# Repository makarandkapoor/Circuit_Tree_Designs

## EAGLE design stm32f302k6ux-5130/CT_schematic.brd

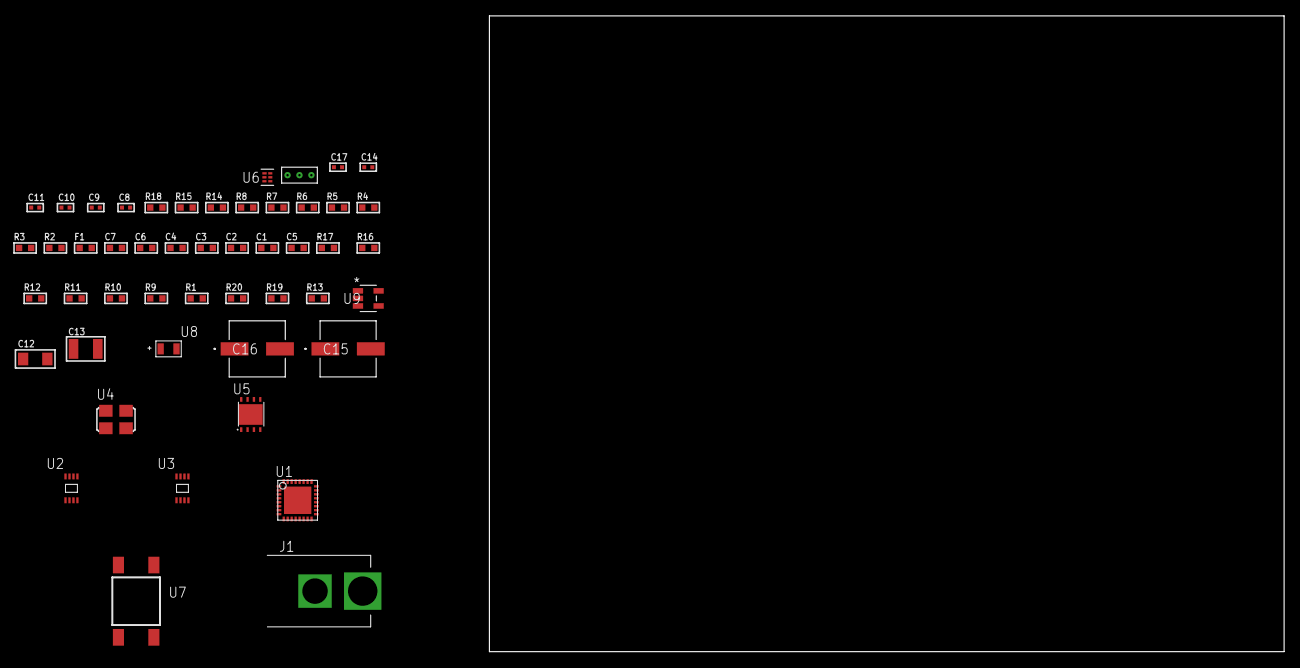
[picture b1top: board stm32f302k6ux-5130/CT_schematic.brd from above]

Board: 2 copper layers, 100.0 x 80.0 mm, 49 parts (0 on the bottom side), 25 nets, no tracks yet.

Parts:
C1, C2, C3, C4: 1e-07; C0603
C5: 4.7e-06; C0603
C6: 1e-08; C0603
C7: 1e-06; C0603
C8, C9, C10, C11, C17: 1e-08; C0402
C12: 1e-05; C1206
C13: 1e-05; C1210
C14: 1e-07; C0402
C15, C16: 0.0001; EXV-9H
F1: 240.0; L0603
J1: PJ-037B; PJ-037B_PACKAGE
R1, R9, R10, R11, R12, R16, R17: 10000.0; R0603
R2, R15: 1000.0; R0603
R3: 1600.5; R0603
R4: 4700.0; R0603
R5, R6, R7, R8: 2200.0; R0603
R13: 100000.0; R0603
R14: 2231.0; R0603
R18: 9100.0; R0603
R19: 680000.0; R0603
R20: 120000.0; R0603
U1: STM32F302K6U6; UFQFPN32
U2: 24AA00T-I/MNY; TDFN-8/6MM
U3: 24AA128T-I/MNY; TDFN-8/6MM
U4: ASFL1-25MHZ-NCS; ASFL1
U5: LP3878SDX-ADJ/NOPB; WSON-8
U6: TPS3895ADRYR; SON-6
U7: 4-1437565-2; SW_4-1437565-2
U8: Q65110A2395; LGM67K-G1J2-24-Z
U9: nc7sz125m5x; NC7SZ125M5X
U10: Dummy; DUMMY_PACKAGE_103

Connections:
CLK_U1_2: U1.2, U4.3
GND: C1.2, C2.2, C3.2, C4.2, C5.2, C6.2, C7.2, C8.2, C9.2, C10.2, C11.2, C12.2, C13.2, C14.2, C15.2, C16.2, C17.2, J1.2, R2.2, R9.2, R12.2, R15.2, R18.2, R20.2, U1.6, U1.16, U1.32, U1.EPAD, U2.4, U3.4, U4.2, U5.3, U5.PAD, U6.2, U8.C, U9.1, U9.3, U10.1
NET_U1_3: R7.1, U1.3, U2.6
NET_U1_4: R4.1, U1.4, U9.4
NET_U1_5: C6.1, C7.1, F1.1, U1.5
NET_U1_20: R8.1, U1.20, U2.5
NET_U1_24: R6.1, U1.24, U3.5
NET_U1_25: R5.1, U1.25, U3.6
NET_U1_29: R3.1, U1.29, U8.A
NET_U1_30: R1.1, U1.30, U7.3, U7.4
NET_U1_31: R9.1, U1.31
NET_U3_1: R10.1, U3.1
NET_U3_2: R11.1, U3.2
NET_U3_3: R12.1, U3.3
NET_U5_1: C11.1, U5.1
NET_U5_6: R14.2, R15.1, U5.6
NET_U5_8: R13.1, U5.8
NET_U6_1: R17.1, R18.1, U6.1
NET_U6_3: R19.2, R20.1, U6.3
NET_U6_4: R16.1, U6.4, U9.2
NET_U7_1: R2.1, U7.1, U7.2
PROC_PA0: U1.7, U10.2
PROC_PA1: U1.8, U10.3
VCC_S1_7V8: C12.1, C15.1, C16.1, J1.1, R13.2, U5.4
VCC_TIER1_3V3: C1.1, C2.1, C3.1, C4.1, C5.1, C8.1, C9.1, C10.1, C13.1, C14.1, C17.1, F1.2, R1.2, R3.2, R4.2, R5.2, R6.2, R7.2, R8.2, R10.2, R11.2, R14.1, R16.2, R17.2, R19.1, U1.1, U1.17, U2.8, U3.7, U3.8, U4.4, U5.5, U6.6, U9.5

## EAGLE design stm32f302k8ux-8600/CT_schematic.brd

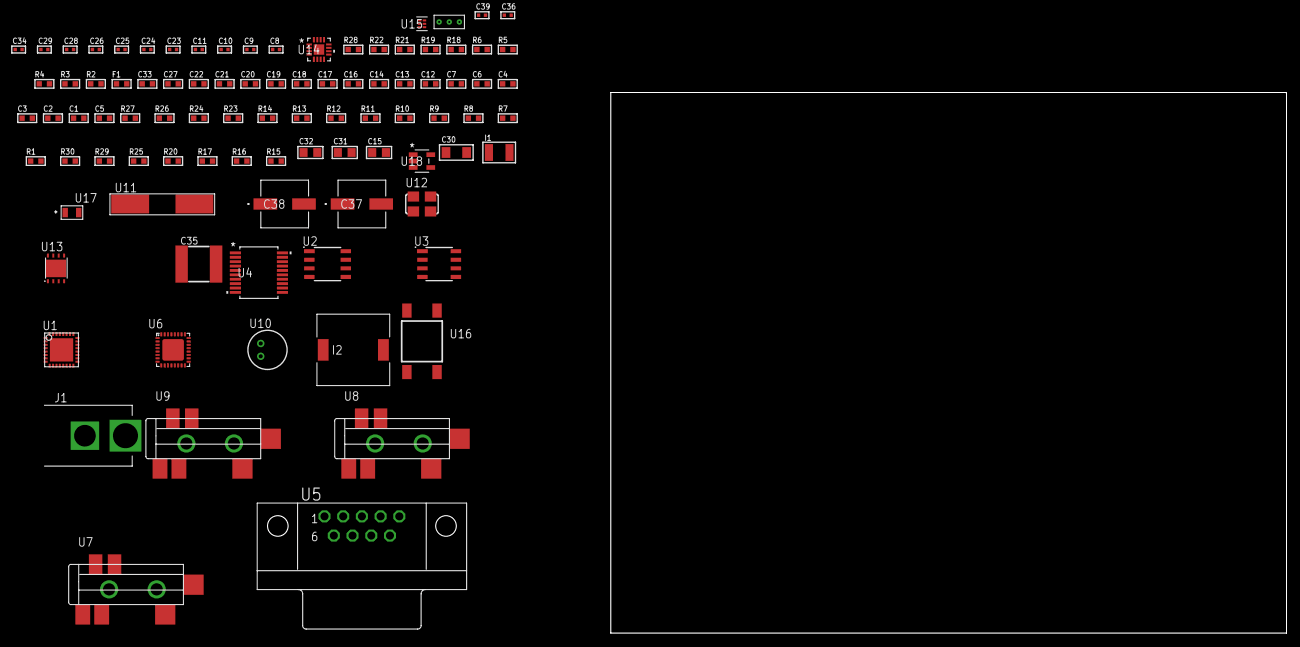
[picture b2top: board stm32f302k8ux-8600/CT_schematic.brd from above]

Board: 2 copper layers, 100.0 x 80.0 mm, 92 parts (0 on the bottom side), 71 nets, no tracks yet.

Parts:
C1, C2, C3, C4: 1e-07; C0603
C5: 4.7e-06; C0603
C6: 1e-08; C0603
C7, C12, C13, C14, C16, C17, C18, C19, C20, C21, C22, C27, C33: 1e-06; C0603
C8, C9: 1e-11; C0402
C10, C11, C28, C29, C39: 1e-08; C0402
C15: 4.7e-06; C0805
C23, C24, C25, C26, C34, C36: 1e-07; C0402
C30: 1e-05; C1206
C31, C32: 1e-05; C0805
C35: 6.8e-05; 2220
C37, C38: 0.0001; EXV-9H
F1: 240.0; L0603
I1: 1.5e-05; L1210
I2: 2.5e-06; DR1040
J1: PJ-037B; PJ-037B_PACKAGE
R1, R7, R8, R9, R10, R11, R12, R13, R14, R26, R27: 10000.0; R0603
R2, R22: 1000.0; R0603
R3: 1600.5; R0603
R4: 4700.0; R0603
R5, R6: 2200.0; R0603
R15, R16, R17, R20: 100000.0; R0603
R18, R19: 1270.0; R0603
R21: 200.0; R0603
R23: 20000.0; R0603
R24: 91000.0; R0603
R25: 300000.0; R0603
R28: 9100.0; R0603
R29: 680000.0; R0603
R30: 120000.0; R0603
U1: STM32F302K8U7; UFQFPN32
U2: AT25160B-SSHL-T; SOIC-8
U3: AT24C02D-SSHM-T; AT24C02D
U4: MAX3218EAP+T; SSOP-20
U5: 182-009-113R531; 182-009-MALE
U6: SGTL5000XNAA3; QFN-32
U7, U8, U9: SJ-43515TS-SMT-TR
U10: WM-64PCT; WM-64PC
U11: ABLS-25.000MHZ-B2F-T
U12: ASFL-24.57MHZ-NCS; ASFL1
U13: LP3878SDX-ADJ/NOPB; WSON-8
U14: LTC3601EUD#PBF; QFN-16_EP
U15: TPS3895ADRYR; SON-6
U16: 4-1437565-2; SW_4-1437565-2
U17: Q65110A2395; LGM67K-G1J2-24-Z
U18: nc7sz125m5x; NC7SZ125M5X
U19: Dummy; DUMMY_PACKAGE_184

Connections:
CLK_CRYSTAL_U1_2: C8.1, U1.2, U11.1
CLK_CRYSTAL_U1_3: C9.1, U1.3, U11.2
CLK_U6_21: U6.21, U12.3
GND: C1.2, C2.2, C3.2, C4.2, C5.2, C6.2, C7.2, C8.2, C9.2, C10.2, C11.2, C12.2, C13.2, C14.2, C23.2, C24.2, C25.2, C26.2, C27.2, C28.2, C29.2, C30.2, C31.2, C32.2, C33.2, C35.1, C35.2, C36.2, C37.2, C38.2, C39.2, J1.2, R2.2, R7.2, R11.2, R13.2, R14.2, R19.2, R22.2, R23.2, R25.2, R28.2, R30.2, U1.6, U1.16, U1.32, U1.EPAD, U2.4, U3.4, U4.5, U4.17, U4.20, U5.5, U6.1, U6.3, U6.7, U6.EXP, U8.1, U9.1, U10.2, U12.2, U13.3, U13.PAD, U14.1, U14.9, U14.17, U15.2, U17.C, U18.1, U18.3, U19.1
NET_U1_4: R4.1, U1.4, U18.4
NET_U1_5: C6.1, C7.1, F1.1, U1.5
NET_U1_24: R6.1, U1.24, U3.5
NET_U1_25: R5.1, U1.25, U3.6
NET_U1_29: R3.1, U1.29, U17.A
NET_U1_30: R1.1, U1.30, U16.3, U16.4
NET_U1_31: R7.1, U1.31
NET_U2_1: R9.1, U2.1
NET_U2_3: R8.1, U2.3
NET_U2_7: R10.1, U2.7
NET_U3_1: R12.1, U3.1
NET_U3_2: R13.1, U3.2
NET_U3_3: R14.1, U3.3
NET_U3_7: R11.1, U3.7
NET_U4_1: I1.1, U4.1
NET_U4_2: R15.1, U4.2
NET_U4_3: R16.1, U4.3
NET_U4_4: R17.1, U4.4
NET_U4_15: C14.1, U4.15
NET_U4_16: C15.2, U4.16
NET_U4_18: C15.1, U4.18
NET_U4_19: C13.1, U4.19
NET_U5_2: U4.12, U5.2
NET_U5_3: U4.14, U5.3
NET_U5_7: U4.11, U5.7
NET_U5_8: U4.13, U5.8
NET_U6_10: C26.1, U6.10
NET_U6_29: R18.1, U6.29
NET_U6_31: R19.1, U6.31
NET_U7_1: U6.4, U7.1
NET_U7_2: U6.2, U7.2
NET_U7_5: U6.6, U7.5
NET_U8_2: C17.1, U8.2
NET_U8_5: C16.1, U8.5
NET_U9_2: C19.1, C20.1, U9.2
NET_U9_5: C18.1, U9.5
NET_U9_13: C19.2, C20.2
NET_U10_1: C21.1, C22.1, C27.1, U6.16, U10.1
NET_U10_15: C21.2, C22.2
NET_U13_1: C29.1, U13.1
NET_U13_6: R21.2, R22.1, U13.6
NET_U13_8: R20.1, U13.8
NET_U14_3: C34.2, I2.1, U14.3, U14.4
NET_U14_6: C34.1, U14.6
NET_U14_7: C33.1, U14.7, U14.12
NET_U14_10: R25.1, U14.10
NET_U14_11: R23.1, R24.1, U14.11
NET_U14_ATNET_3: I2.2, R24.2
NET_U15_1: R27.1, R28.1, U15.1
NET_U15_3: R29.2, R30.1, U15.3
NET_U15_4: R26.1, U15.4, U18.2
NET_U16_1: R2.1, U16.1, U16.2
PROC_I2S3_CK: U1.26, U6.24
PROC_I2S3_EXT_SD: U1.27, U6.25
PROC_I2S3_SD: U1.28, U6.26
PROC_I2S3_WS: U1.11, U6.23
PROC_PA5: U1.12, U19.2
PROC_PA6: U1.13, U19.3
PROC_SPI2_MISO: U1.20, U2.2
PROC_SPI2_MOSI: U1.21, U2.5
PROC_USART2_CTS: U1.7, U4.8
PROC_USART2_RTS: U1.8, U4.10
PROC_USART2_RX: U1.10, U4.9
PROC_USART2_TX: U1.9, U4.7
VCC_S1_4V7: C30.1, C32.1, C37.1, C38.1, J1.1, R20.2, U13.4, U14.15, U14.16
VCC_TIER1_1V2: C23.1, C31.1, R21.1, U6.30, U13.5
VCC_TIER1_3V3: C1.1, C2.1, C3.1, C4.1, C5.1, C10.1, C11.1, C12.1, C24.1, C25.1, C28.1, C35.2, C36.1, C39.1, F1.2, I1.2, I2.2, R1.2, R3.2, R4.2, R5.2, R6.2, R8.2, R9.2, R10.2, R12.2, R15.2, R16.2, R17.2, R18.2, R24.2, R26.2, R27.2, R29.1, U1.1, U1.17, U2.8, U3.8, U4.6, U6.5, U6.20, U12.4, U14.8, U15.6, U18.5

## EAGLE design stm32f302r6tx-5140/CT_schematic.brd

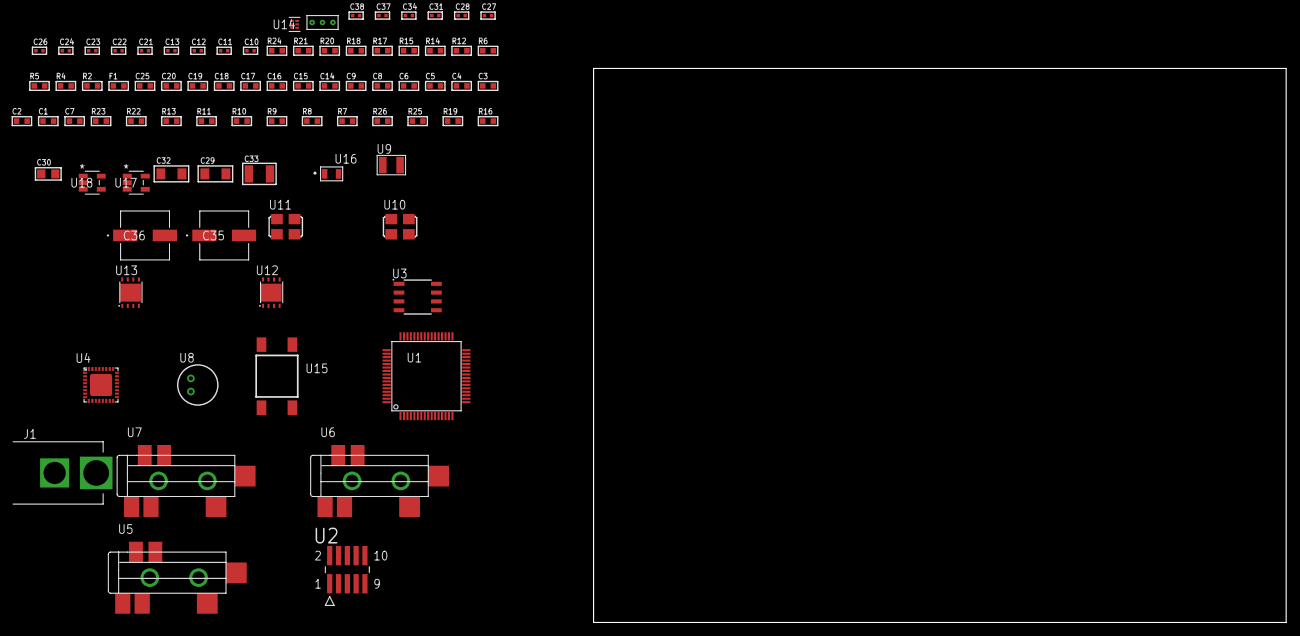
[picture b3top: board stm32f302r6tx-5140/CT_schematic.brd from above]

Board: 2 copper layers, 100.0 x 80.0 mm, 83 parts (0 on the bottom side), 50 nets, no tracks yet.

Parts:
C1, C9, C14, C15, C16, C17, C18, C19, C20, C25: 1e-06; C0603
C2, C3, C4, C5, C6: 1e-07; C0603
C7: 4.7e-06; C0603
C8: 1e-08; C0603
C10, C11: 1e-11; C0402
C12, C21, C22, C23, C24, C34: 1e-07; C0402
C13, C26, C27, C28, C31, C37, C38: 1e-08; C0402
C29, C32: 1e-05; C1206
C30: 1e-05; C0805
C33: 1e-05; C1210
C35, C36: 0.0001; EXV-9H
F1: 240.0; L0603
J1: PJ-037B; PJ-037B_PACKAGE
R2, R18, R21: 1000.0; R0603
R4: 4700.0; R0603
R5, R6: 2200.0; R0603
R7, R8, R9, R10, R11, R13, R22, R23: 10000.0; R0603
R12: 5.0; R0603
R14, R15: 1270.0; R0603
R16, R19: 100000.0; R0603
R17: 200.0; R0603
R20: 2231.0; R0603
R24: 9100.0; R0603
R25: 680000.0; R0603
R26: 120000.0; R0603
U1: STM32F302R6T6; LQFP64
U2: FTSH-105-01-L-DV-K; SAMTEC_FTSH-105-01-L-DV-K
U3: M24M02-DRMN6TP; SOIC-8
U4: SGTL5000XNAA3; QFN-32
U5, U6, U7: SJ-43515TS-SMT-TR
U8: WM-64PCT; WM-64PC
U9: ABS07-32.768KHZ-7-T
U10: ASFL-24.57MHZ-NCS; ASFL1
U11: ASFL1-25MHZ-NCS; ASFL1
U12, U13: LP3878SDX-ADJ/NOPB; WSON-8
U14: TPS3895ADRYR; SON-6
U15: 4-1437565-2; SW_4-1437565-2
U16: Q65110A2395; LGM67K-G1J2-24-Z
U17, U18: nc7sz125m5x; NC7SZ125M5X
U19: Dummy; DUMMY_PACKAGE_173

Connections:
CLK_CRYSTAL_U1_3: C10.1, U1.3, U9.1
CLK_CRYSTAL_U1_4: C11.1, U1.4, U9.2
CLK_U1_5: U1.5, U11.3
CLK_U4_21: U4.21, U10.3
GND: C1.2, C2.2, C3.2, C4.2, C5.2, C6.2, C7.2, C8.2, C9.2, C10.2, C11.2, C12.2, C13.2, C21.2, C22.2, C23.2, C24.2, C25.2, C26.2, C27.2, C28.2, C29.2, C30.2, C31.2, C32.2, C33.2, C34.2, C35.2, C36.2, C37.2, C38.2, J1.2, R2.2, R7.2, R11.2, R12.2, R13.2, R15.2, R18.2, R21.2, R24.2, R26.2, U1.12, U1.18, U1.31, U1.47, U1.63, U2.3, U2.5, U3.4, U4.1, U4.3, U4.7, U4.EXP, U6.1, U7.1, U8.2, U10.2, U11.2, U12.3, U12.PAD, U13.3, U13.PAD, U14.2, U16.C, U17.2, U17.3, U18.1, U18.3, U19.1
NET_U1_7: R4.1, U1.7, U18.4
NET_U1_13: C8.1, C9.1, F1.1, U1.13
NET_U1_58: R5.1, U1.58, U3.6
NET_U1_59: R6.1, U1.59, U3.5
NET_U1_60: R7.1, U1.60
NET_U1_62: U15.3, U15.4
NET_U2_9: R12.1, U2.9
NET_U3_3: R13.1, U3.3
NET_U4_10: C24.1, U4.10
NET_U4_29: R14.1, U4.29
NET_U4_31: R15.1, U4.31
NET_U5_1: U4.4, U5.1
NET_U5_2: U4.2, U5.2
NET_U5_5: U4.6, U5.5
NET_U6_2: C15.1, U6.2
NET_U6_5: C14.1, U6.5
NET_U7_2: C17.1, C18.1, U7.2
NET_U7_5: C16.1, U7.5
NET_U7_13: C17.2, C18.2
NET_U8_1: C19.1, C20.1, C25.1, U4.16, U8.1
NET_U8_15: C19.2, C20.2
NET_U12_1: C28.1, U12.1
NET_U12_6: R17.2, R18.1, U12.6
NET_U12_8: R16.1, U12.8
NET_U13_1: C31.1, U13.1
NET_U13_6: R20.2, R21.1, U13.6
NET_U13_8: R19.1, U13.8
NET_U14_1: R23.1, R24.1, U14.1
NET_U14_3: R25.2, R26.1, U14.3
NET_U14_4: R22.1, U14.4, U17.4, U18.2
NET_U15_1: R2.1, U15.1, U15.2
PROC_I2S2_CK: U1.6, U4.24
PROC_I2S2_EXT_SD: U1.35, U4.25
PROC_I2S2_SD: U1.36, U4.26
PROC_I2S2_WS: U1.33, U4.23
PROC_PC0: U1.8, U19.3
PROC_PC13: U1.2, U19.2
PROC_SYS_JTCK_SWCLK: R11.1, U1.49, U2.4
PROC_SYS_JTDI: R9.1, U1.50, U2.8
PROC_SYS_JTDO_TRACESWO: U1.55, U2.6
PROC_SYS_JTMS_SWDIO: R10.1, U1.46, U2.2
RST_OUT_U2_JTAG_RST_B: R8.1, U2.10, U17.1
VCC_S1_5V6: C29.1, C32.1, C35.1, C36.1, J1.1, R16.2, R19.2, U12.4, U13.4
VCC_TIER1_1V2: C21.1, C30.1, R17.1, U4.30, U12.5
VCC_TIER1_3V3: C1.1, C2.1, C3.1, C4.1, C5.1, C6.1, C7.1, C12.1, C13.1, C22.1, C23.1, C26.1, C27.1, C33.1, C34.1, C37.1, C38.1, F1.2, R4.2, R5.2, R6.2, R8.2, R9.2, R10.2, R14.2, R20.1, R22.2, R23.2, R25.1, U1.1, U1.19, U1.32, U1.48, U1.64, U2.1, U3.8, U4.5, U4.20, U10.4, U11.4, U13.5, U14.6, U17.5, U18.5

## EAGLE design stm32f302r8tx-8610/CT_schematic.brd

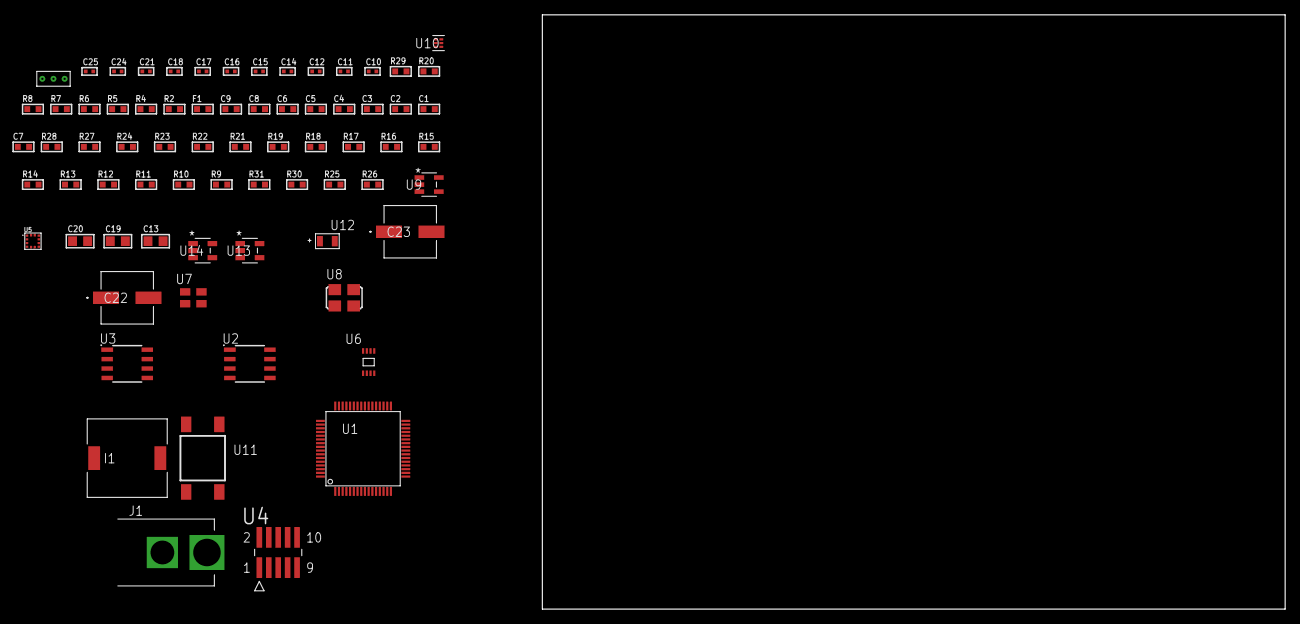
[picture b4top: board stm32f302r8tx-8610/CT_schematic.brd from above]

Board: 2 copper layers, 100.0 x 80.0 mm, 72 parts (0 on the bottom side), 44 nets, no tracks yet.

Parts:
C1, C9: 1e-06; C0603
C2, C3, C4, C5, C6: 1e-07; C0603
C7: 4.7e-06; C0603
C8: 1e-08; C0603
C10, C11, C16, C17, C18, C24, C25: 1e-08; C0402
C12, C14, C15, C21: 1e-07; C0402
C13, C19, C20: 1e-05; C0805
C22, C23: 0.0001; EXV-9H
F1: 240.0; L0603
I1: 7e-06; DR1040
J1: PJ-037B; PJ-037B_PACKAGE
R2: 1000.0; R0603
R4: 4700.0; R0603
R5, R6, R7, R8: 2200.0; R0603
R9, R10, R11, R12, R13, R14, R15, R16, R17, R18, R19, R21, R22, R23, R24, R27, R28: 10000.0; R0603
R20: 5.0; R0603
R25: 220000.0; R0603
R26: 1000000.0; R0603
R29: 9100.0; R0603
R30: 680000.0; R0603
R31: 120000.0; R0603
U1: STM32F302R8T7; LQFP64
U2: AT25010B-SSHL-T; SOIC-8
U3: AT25640B-SSHL-T; SOIC-8
U4: FTSH-105-01-L-DV-K; SAMTEC_FTSH-105-01-L-DV-K
U5: LIS2HH12TR; LGA-12
U6: 24AA64T-I/MNY; TDFN-8/6MM
U7: ASEK-32.768KHz-ECST; ASEK
U8: ASFL1-25MHZ-NCS; ASFL1
U9: ltc3406es5; TSOT-23-5
U10: TPS3895ADRYR; SON-6
U11: 4-1437565-2; SW_4-1437565-2
U12: Q65110A2395; LGM67K-G1J2-24-Z
U13, U14: nc7sz125m5x; NC7SZ125M5X
U15: Dummy; DUMMY_PACKAGE_160

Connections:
CLK_U1_3: U1.3, U7.3
CLK_U1_5: U1.5, U8.3
GND: C1.2, C2.2, C3.2, C4.2, C5.2, C6.2, C7.2, C8.2, C9.2, C10.2, C11.2, C12.2, C13.2, C14.2, C15.2, C16.2, C17.2, C18.2, C19.2, C20.1, C20.2, C21.2, C22.2, C23.2, C24.2, C25.2, J1.2, R2.2, R9.2, R19.2, R20.2, R23.2, R25.2, R29.2, R31.2, U1.12, U1.18, U1.31, U1.47, U1.63, U2.4, U3.4, U4.3, U4.5, U5.5, U5.6, U5.7, U5.8, U6.4, U6.7, U7.2, U8.2, U9.2, U10.2, U12.C, U13.2, U13.3, U14.1, U14.3, U15.1
NET_U1_7: R4.1, U1.7, U14.4
NET_U1_13: C8.1, C9.1, F1.1, U1.13
NET_U1_42: R7.1, U1.42, U6.6
NET_U1_43: R8.1, U1.43, U6.5
NET_U1_58: R5.1, U1.58, U5.1
NET_U1_59: R6.1, U1.59, U5.4
NET_U1_60: R9.1, U1.60
NET_U1_62: U11.3, U11.4
NET_U2_3: R10.1, U2.3
NET_U2_7: R12.1, U2.7
NET_U3_3: R13.1, U3.3
NET_U3_7: R15.1, U3.7
NET_U4_9: R20.1, U4.9
NET_U5_2: R21.1, U5.2
NET_U6_1: R22.1, U6.1
NET_U6_2: R23.1, U6.2
NET_U6_3: R24.1, U6.3
NET_U9_3: I1.1, U9.3
NET_U9_5: R25.1, R26.1, U9.5
NET_U9_ATNET_3: I1.2, R26.2
NET_U10_1: R28.1, R29.1, U10.1
NET_U10_3: R30.2, R31.1, U10.3
NET_U10_4: R27.1, U10.4, U13.4, U14.2
NET_U11_1: R2.1, U11.1, U11.2
PROC_PC13: U1.2, U15.2
PROC_PC15_OSC32_OUT: U1.4, U15.3
PROC_SPI2_MISO: U1.35, U3.2
PROC_SPI2_MOSI: U1.36, U3.5
PROC_SPI2_NSS: R14.1, U1.33, U3.1
PROC_SPI2_SCK: U1.6, U3.6
PROC_SPI3_MISO: U1.52, U2.2
PROC_SPI3_MOSI: U1.53, U2.5
PROC_SPI3_NSS: R11.1, U1.20, U2.1
PROC_SPI3_SCK: U1.51, U2.6
PROC_SYS_JTCK_SWCLK: R19.1, U1.49, U4.4
PROC_SYS_JTDI: R17.1, U1.50, U4.8
PROC_SYS_JTDO_TRACESWO: U1.55, U4.6
PROC_SYS_JTMS_SWDIO: R18.1, U1.46, U4.2
RST_OUT_U4_JTAG_RST_B: R16.1, U4.10, U13.1
VCC_S1_5V4: C19.1, C22.1, C23.1, J1.1, U9.4
VCC_TIER1_3V3: C1.1, C2.1, C3.1, C4.1, C5.1, C6.1, C7.1, C10.1, C11.1, C12.1, C13.1, C14.1, C15.1, C16.1, C17.1, C18.1, C20.2, C21.1, C24.1, C25.1, F1.2, I1.2, R4.2, R5.2, R6.2, R7.2, R8.2, R10.2, R11.2, R12.2, R13.2, R14.2, R15.2, R16.2, R17.2, R18.2, R21.2, R22.2, R24.2, R26.2, R27.2, R28.2, R30.1, U1.1, U1.19, U1.32, U1.48, U1.64, U2.8, U3.8, U4.1, U5.9, U5.10, U6.8, U7.4, U8.4, U10.6, U13.5, U14.5

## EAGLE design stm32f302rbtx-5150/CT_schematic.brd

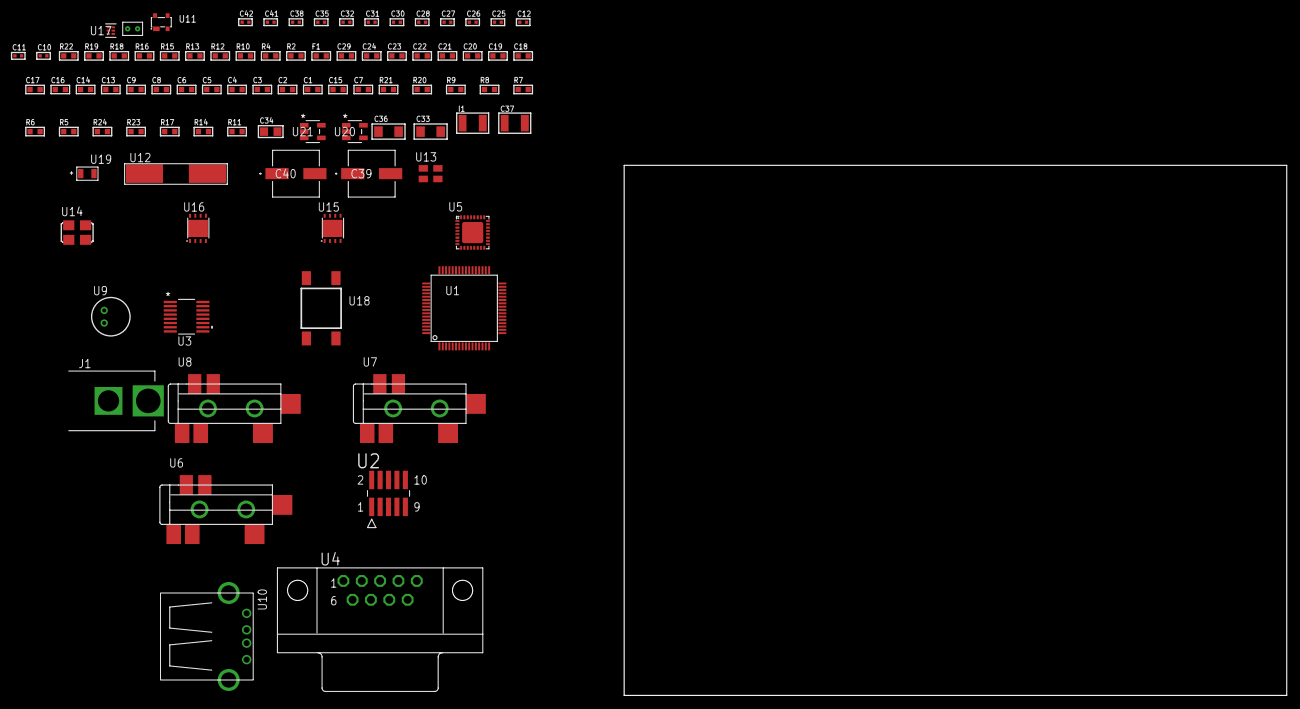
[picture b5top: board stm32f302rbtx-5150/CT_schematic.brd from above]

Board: 2 copper layers, 100.0 x 80.0 mm, 89 parts (0 on the bottom side), 60 nets, no tracks yet.

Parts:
C1, C9, C13, C14, C16, C17, C18, C19, C20, C21, C22, C23, C24, C29: 1e-06; C0603
C2, C3, C4, C5, C6: 1e-07; C0603
C7: 4.7e-06; C0603
C8: 1e-08; C0603
C10, C11: 1e-11; C0402
C12, C25, C26, C27, C28, C38: 1e-07; C0402
C15: 2.2e-07; C0603
C30, C31, C32, C35, C41, C42: 1e-08; C0402
C33, C36: 1e-05; C1206
C34: 1e-05; C0805
C37: 1e-05; C1210
C39, C40: 0.0001; EXV-9H
F1: 240.0; L0603
I1: 1e-05; L1210
J1: PJ-037B; PJ-037B_PACKAGE
R2, R16, R19: 1000.0; R0603
R4: 4700.0; R0603
R5, R6, R7, R8, R9, R20, R21: 10000.0; R0603
R10: 5.0; R0603
R11, R14, R17: 100000.0; R0603
R12, R13: 1270.0; R0603
R15: 200.0; R0603
R18: 2231.0; R0603
R22: 9100.0; R0603
R23: 680000.0; R0603
R24: 120000.0; R0603
U1: STM32F302RBT7; LQFP64
U2: FTSH-105-01-L-DV-K; SAMTEC_FTSH-105-01-L-DV-K
U3: LTC2804CGN-1#PBF; SSOP-16
U4: 182-009-113R531; 182-009-MALE
U5: SGTL5000XNAA3; QFN-32
U6, U7, U8: SJ-43515TS-SMT-TR
U9: WM-64PCT; WM-64PC
U10: 61400416021; USB-A-H
U11: prtr5v0u2ax; SOT143B
U12: ABLS-25.000MHZ-B2F-T
U13: ASEK-32.768KHz-ECST; ASEK
U14: ASFL-24.57MHZ-NCS; ASFL1
U15, U16: LP3878SDX-ADJ/NOPB; WSON-8
U17: TPS3895ADRYR; SON-6
U18: 4-1437565-2; SW_4-1437565-2
U19: Q65110A2395; LGM67K-G1J2-24-Z
U20, U21: nc7sz125m5x; NC7SZ125M5X
U22: Dummy; DUMMY_PACKAGE_184

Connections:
CLK_CRYSTAL_U1_5: C10.1, U1.5, U12.1
CLK_CRYSTAL_U1_6: C11.1, U1.6, U12.2
CLK_U1_3: U1.3, U13.3
CLK_U5_21: U5.21, U14.3
GND: C1.2, C2.2, C3.2, C4.2, C5.2, C6.2, C7.2, C8.2, C9.2, C10.2, C11.2, C12.2, C13.2, C14.2, C16.2, C17.2, C25.2, C26.2, C27.2, C28.2, C29.2, C30.2, C31.2, C32.2, C33.2, C34.2, C35.2, C36.2, C37.2, C38.2, C39.2, C40.2, C41.2, C42.2, J1.2, R2.2, R5.2, R9.2, R10.2, R13.2, R16.2, R19.2, R22.2, R24.2, U1.12, U1.31, U1.47, U1.63, U2.3, U2.5, U3.8, U4.5, U5.1, U5.3, U5.7, U5.EXP, U7.1, U8.1, U9.2, U10.4, U10.5, U10.6, U11.1, U13.2, U14.2, U15.3, U15.PAD, U16.3, U16.PAD, U17.2, U19.C, U20.2, U20.3, U21.1, U21.3, U22.1
NET_U1_7: R4.1, U1.7, U21.4
NET_U1_13: C8.1, C9.1, F1.1, U1.13
NET_U1_60: R5.1, U1.60
NET_U1_62: U18.3, U18.4
NET_U2_9: R10.1, U2.9
NET_U3_6: C13.1, U3.6
NET_U3_7: C15.1, I1.2, U3.7
NET_U3_9: C14.1, U3.9
NET_U3_10: C15.2, U3.10
NET_U3_11: R11.1, U3.11
NET_U4_2: U3.1, U4.2
NET_U4_3: U3.3, U4.3
NET_U4_7: U3.2, U4.7
NET_U4_8: U3.4, U4.8
NET_U5_10: C28.1, U5.10
NET_U5_29: R12.1, U5.29
NET_U5_31: R13.1, U5.31
NET_U6_1: U5.4, U6.1
NET_U6_2: U5.2, U6.2
NET_U6_5: U5.6, U6.5
NET_U7_2: C19.1, U7.2
NET_U7_5: C18.1, U7.5
NET_U8_2: C21.1, C22.1, U8.2
NET_U8_5: C20.1, U8.5
NET_U8_13: C21.2, C22.2
NET_U9_1: C23.1, C24.1, C29.1, U5.16, U9.1
NET_U9_15: C23.2, C24.2
NET_U11_4: U10.1, U11.4
NET_U15_1: C32.1, U15.1
NET_U15_6: R15.2, R16.1, U15.6
NET_U15_8: R14.1, U15.8
NET_U16_1: C35.1, U16.1
NET_U16_6: R18.2, R19.1, U16.6
NET_U16_8: R17.1, U16.8
NET_U17_1: R21.1, R22.1, U17.1
NET_U17_3: R23.2, R24.1, U17.3
NET_U17_4: R20.1, U17.4, U20.4, U21.2
NET_U18_1: R2.1, U18.1, U18.2
PROC_DAC_OUT1: U1.20, U22.2
PROC_I2S2_CK: U1.34, U5.24
PROC_I2S2_EXT_SD: U1.35, U5.25
PROC_I2S2_SD: U1.36, U5.26
PROC_I2S2_WS: U1.33, U5.23
PROC_SYS_JTCK_SWCLK: R9.1, U1.49, U2.4
PROC_SYS_JTDI: R7.1, U1.50, U2.8
PROC_SYS_JTDO_TRACESWO: U1.55, U2.6
PROC_SYS_JTMS_SWDIO: R8.1, U1.46, U2.2
PROC_UART4_RX: U1.52, U3.16
PROC_UART4_TX: U1.51, U3.14
PROC_USB_DM: U10.2, U11.3
PROC_USB_DP: U10.3, U11.2
RST_OUT_U2_JTAG_RST_B: R6.1, U2.10, U20.1
VCC_S1_5V3: C33.1, C36.1, C39.1, C40.1, J1.1, R14.2, R17.2, U15.4, U16.4
VCC_TIER1_1V2: C25.1, C34.1, R15.1, U5.30, U15.5
VCC_TIER1_3V3: C1.1, C2.1, C3.1, C4.1, C5.1, C6.1, C7.1, C12.1, C16.1, C17.1, C26.1, C27.1, C30.1, C31.1, C37.1, C38.1, C41.1, C42.1, F1.2, I1.1, R4.2, R6.2, R7.2, R8.2, R11.2, R12.2, R18.1, R20.2, R21.2, R23.1, U1.1, U1.19, U1.32, U1.48, U1.64, U2.1, U3.5, U3.12, U5.5, U5.20, U13.4, U14.4, U16.5, U17.6, U20.5, U21.5

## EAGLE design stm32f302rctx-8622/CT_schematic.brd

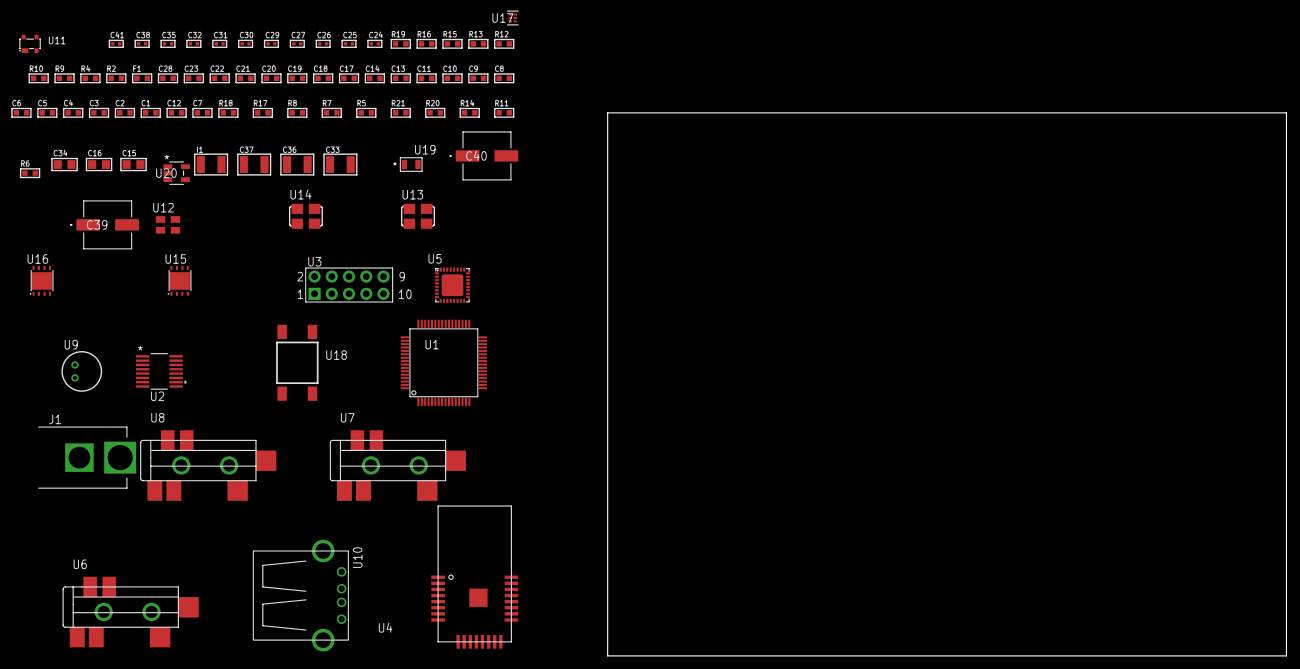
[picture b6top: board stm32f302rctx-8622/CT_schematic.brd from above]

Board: 2 copper layers, 100.0 x 80.0 mm, 83 parts (0 on the bottom side), 58 nets, no tracks yet.

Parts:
C1, C9, C10, C11, C13, C14, C17, C18, C19, C20, C21, C22, C23, C28: 1e-06; C0603
C2, C3, C4, C5, C6: 1e-07; C0603
C7: 4.7e-06; C0603
C8: 1e-08; C0603
C12: 2.2e-07; C0603
C15, C16, C34: 1e-05; C0805
C24, C25, C26, C27, C38: 1e-07; C0402
C29, C30, C31, C32, C35, C41: 1e-08; C0402
C33, C36, C37: 1e-05; C1210
C39, C40: 0.0001; EXV-9H
F1: 240.0; L0603
I1: 1e-05; L1210
J1: PJ-037B; PJ-037B_PACKAGE
R2, R13, R16: 1000.0; R0603
R4: 4700.0; R0603
R5, R7, R8, R17, R18: 10000.0; R0603
R6, R11, R14: 100000.0; R0603
R9, R10: 1270.0; R0603
R12: 200.0; R0603
R15: 2231.0; R0603
R19: 9100.0; R0603
R20: 680000.0; R0603
R21: 120000.0; R0603
U1: STM32F302RCT6; LQFP64
U2: LTC2804CGN-1#PBF; SSOP-16
U3: HTSS-105-01-G-D
U4: ATBTLC1000-MR110CA
U5: SGTL5000XNAA3; QFN-32
U6, U7, U8: SJ-43515TS-SMT-TR
U9: WM-64PCT; WM-64PC
U10: 61400416021; USB-A-H
U11: prtr5v0u2ax; SOT143B
U12: ASEK-32.768KHz-ECST; ASEK
U13: ASFL-24.57MHZ-NCS; ASFL1
U14: ASFL1-25MHZ-NCS; ASFL1
U15, U16: LP3878SDX-ADJ/NOPB; WSON-8
U17: TPS3895ADRYR; SON-6
U18: 4-1437565-2; SW_4-1437565-2
U19: Q65110A2395; LGM67K-G1J2-24-Z
U20: nc7sz125m5x; NC7SZ125M5X

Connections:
CLK_U1_3: U1.3, U12.3
CLK_U1_5: U1.5, U14.3
CLK_U5_21: U5.21, U13.3
GND: C1.2, C2.2, C3.2, C4.2, C5.2, C6.2, C7.2, C8.2, C9.2, C10.2, C11.2, C13.2, C14.2, C15.2, C16.2, C24.2, C25.2, C26.2, C27.2, C28.2, C29.2, C30.2, C31.2, C32.2, C33.2, C34.2, C35.2, C36.2, C37.2, C38.2, C39.2, C40.2, C41.2, J1.2, R2.2, R5.2, R10.2, R13.2, R16.2, R19.2, R21.2, U1.12, U1.31, U1.47, U1.63, U2.8, U3.9, U4.1, U4.9, U4.13, U4.24, U4.25, U5.1, U5.3, U5.7, U5.EXP, U7.1, U8.1, U9.2, U10.4, U10.5, U10.6, U11.1, U12.2, U13.2, U14.2, U15.3, U15.PAD, U16.3, U16.PAD, U17.2, U19.C, U20.1, U20.3
NET_U1_7: R4.1, U1.7, U20.4
NET_U1_13: C8.1, C9.1, F1.1, U1.13
NET_U1_60: R5.1, U1.60
NET_U1_62: U18.3, U18.4
NET_U2_6: C10.1, U2.6
NET_U2_7: C12.1, I1.2, U2.7
NET_U2_9: C11.1, U2.9
NET_U2_10: C12.2, U2.10
NET_U2_11: R6.1, U2.11
NET_U3_3: U2.1, U3.3
NET_U3_4: U2.2, U3.4
NET_U3_5: U2.3, U3.5
NET_U3_6: U2.4, U3.6
NET_U4_17: R7.1, U4.17
NET_U4_20: R8.1, U4.20
NET_U5_10: C27.1, U5.10
NET_U5_29: R9.1, U5.29
NET_U5_31: R10.1, U5.31
NET_U6_1: U5.4, U6.1
NET_U6_2: U5.2, U6.2
NET_U6_5: U5.6, U6.5
NET_U7_2: C18.1, U7.2
NET_U7_5: C17.1, U7.5
NET_U8_2: C20.1, C21.1, U8.2
NET_U8_5: C19.1, U8.5
NET_U8_13: C20.2, C21.2
NET_U9_1: C22.1, C23.1, C28.1, U5.16, U9.1
NET_U9_15: C22.2, C23.2
NET_U11_4: U10.1, U11.4
NET_U15_1: C32.1, U15.1
NET_U15_6: R12.2, R13.1, U15.6
NET_U15_8: R11.1, U15.8
NET_U16_1: C35.1, U16.1
NET_U16_6: R15.2, R16.1, U16.6
NET_U16_8: R14.1, U16.8
NET_U17_1: R18.1, R19.1, U17.1
NET_U17_3: R20.2, R21.1, U17.3
NET_U17_4: R17.1, U17.4, U20.2
NET_U18_1: R2.1, U18.1, U18.2
PROC_I2S2_CK: U1.34, U5.24
PROC_I2S2_EXT_SD: U1.35, U5.25
PROC_I2S2_SD: U1.36, U5.26
PROC_I2S2_WS: U1.33, U5.23
PROC_SPI1_MISO: U1.22, U4.14
PROC_SPI1_MOSI: U1.23, U4.11
PROC_SPI1_NSS: U1.20, U4.12
PROC_SPI1_SCK: U1.21, U4.10
PROC_UART4_RX: U1.52, U2.16
PROC_UART4_TX: U1.51, U2.14
PROC_USB_DM: U1.44, U10.2, U11.3
PROC_USB_DP: U1.45, U10.3, U11.2
VCC_S1_15V3: C33.1, C36.1, C39.1, C40.1, J1.1, R11.2, R14.2, U15.4, U16.4
VCC_TIER1_1V2: C24.1, C34.1, R12.1, U5.30, U15.5
VCC_TIER1_3V3: C1.1, C2.1, C3.1, C4.1, C5.1, C6.1, C7.1, C13.1, C14.1, C15.1, C16.1, C25.1, C26.1, C29.1, C30.1, C31.1, C37.1, C38.1, C41.1, F1.2, I1.1, R4.2, R6.2, R7.2, R8.2, R9.2, R15.1, R17.2, R18.2, R20.1, U1.1, U1.19, U1.32, U1.48, U1.64, U2.5, U2.12, U4.6, U4.22, U5.5, U5.20, U12.4, U13.4, U14.4, U16.5, U17.6, U20.5

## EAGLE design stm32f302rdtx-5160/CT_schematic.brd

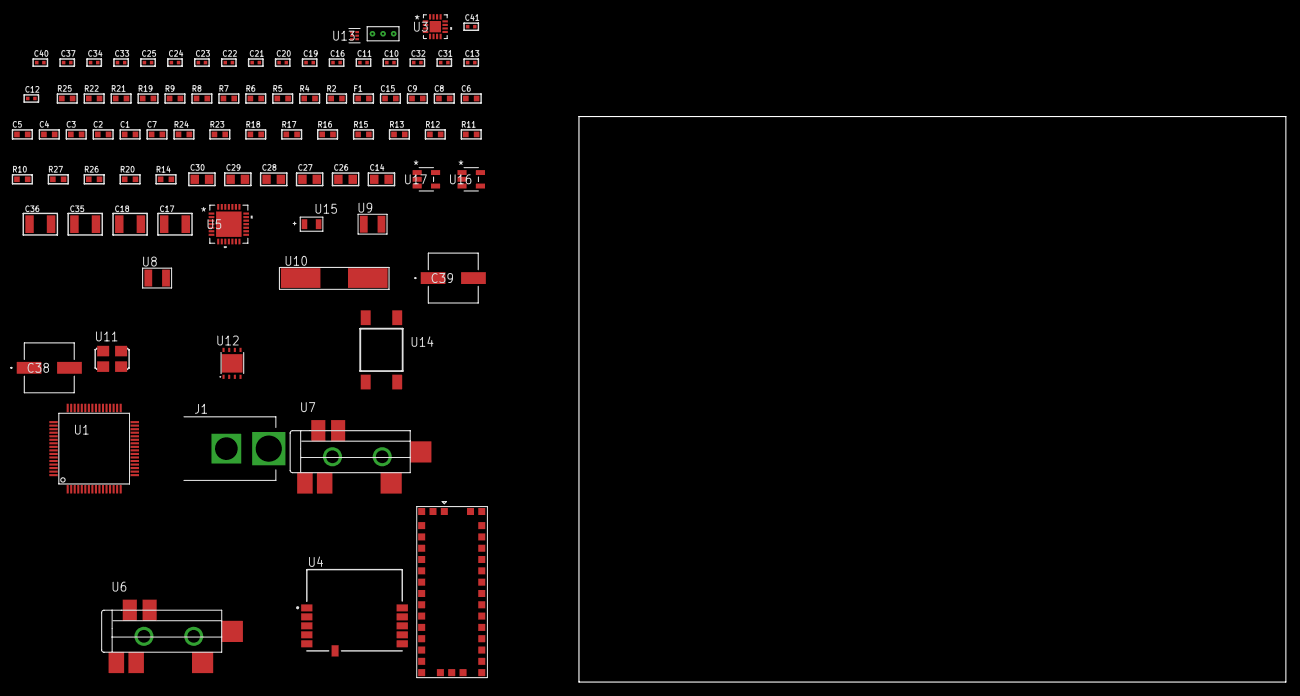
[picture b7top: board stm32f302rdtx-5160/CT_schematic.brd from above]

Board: 2 copper layers, 100.0 x 80.0 mm, 86 parts (0 on the bottom side), 43 nets, no tracks yet.

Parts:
C1, C9, C15: 1e-06; C0603
C2, C3, C4, C5, C6: 1e-07; C0603
C7: 4.7e-06; C0603
C8: 1e-08; C0603
C10, C11: 1e-11; C0402
C12, C13, C31, C32: 2.2e-11; C0402
C14: 4.7e-06; C0805
C16, C21, C22, C23, C24, C25, C37: 1e-07; C0402
C17, C18: 2.2e-05; C1210
C19, C20: 1e-09; C0402
C26, C27, C28, C29, C30: 1e-05; C0805
C33, C34, C40, C41: 1e-08; C0402
C35, C36: 1e-05; C1210
C38, C39: 0.0001; EXV-9H
F1: 240.0; L0603
J1: PJ-037B; PJ-037B_PACKAGE
R2, R22: 1000.0; R0603
R4, R5: 4700.0; R0603
R6, R7, R8, R9: 2200.0; R0603
R10, R11, R12, R13, R23, R24: 10000.0; R0603
R14, R20: 100000.0; R0603
R15, R16, R17, R18: 47000.0; R0603
R19: 680.0; R0603
R21: 2231.0; R0603
R25: 9100.0; R0603
R26: 680000.0; R0603
R27: 120000.0; R0603
U1: STM32F302RDT7; LQFP64
U2: M10382
U3: M41T65Q6F; M41T65_QFN-16
U4: SPBTLE-RF; XCVR_SPBTLE-RF
U5: WM8731CLSEFL; QFN-28
U6, U7: SJ-43515TS-SMT-TR
U8, U9: ABS07-32.768KHZ-7-T
U10: ABLS-12.288MHZ-B4-T
U11: ASFL1-25MHZ-NCS; ASFL1
U12: LP3878SDX-ADJ/NOPB; WSON-8
U13: TPS3895ADRYR; SON-6
U14: 4-1437565-2; SW_4-1437565-2
U15: Q65110A2395; LGM67K-G1J2-24-Z
U16, U17: nc7sz125m5x; NC7SZ125M5X
U18: Dummy; DUMMY_PACKAGE_180

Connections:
CLK_CRYSTAL_U1_3: C10.1, U1.3, U9.1
CLK_CRYSTAL_U1_4: C11.1, U1.4, U9.2
CLK_CRYSTAL_U3_1: U3.1, U8.1
CLK_CRYSTAL_U3_2: U3.2, U8.2
CLK_CRYSTAL_U5_1: C31.1, U5.1, U10.1
CLK_CRYSTAL_U5_2: C32.1, U5.2, U10.2
CLK_U1_5: U1.5, U11.3
GND: C1.2, C2.2, C3.2, C4.2, C5.2, C6.2, C7.2, C8.2, C9.2, C10.2, C11.2, C12.2, C13.2, C14.2, C15.2, C16.2, C20.2, C21.2, C22.2, C23.2, C24.2, C25.2, C26.2, C27.2, C28.2, C29.2, C30.2, C31.2, C32.2, C33.2, C34.2, C35.2, C36.2, C37.2, C38.2, C39.2, C40.2, C41.2, J1.2, R2.2, R10.2, R14.2, R15.2, R16.2, R17.2, R18.2, R22.2, R25.2, R27.2, U1.12, U1.18, U1.31, U1.47, U1.63, U2.2, U2.4, U2.14, U2.17, U2.21, U2.24, U2.26, U2.28, U2.33, U2.34, U2.35, U2.36, U3.3, U3.5, U3.17, U4.6, U5.4, U5.15, U5.19, U5.25, U5.26, U5.29, U6.1, U7.1, U11.2, U12.3, U12.PAD, U13.2, U15.C, U16.1, U16.3, U17.1, U17.3, U18.1
NET_U1_7: R5.1, U1.7, U17.4
NET_U1_13: C8.1, C9.1, F1.1, U1.13
NET_U1_42: R8.1, U1.42, U3.10
NET_U1_43: R9.1, U1.43, U3.9
NET_U1_49: R7.1, U1.49, U2.18
NET_U1_50: R6.1, U1.50, U2.19
NET_U1_60: R10.1, U1.60
NET_U1_62: U14.3, U14.4
NET_U3_4: R11.1, U3.4
NET_U3_11: R12.1, U3.11
NET_U4_11: R4.1, U4.11, U16.4
NET_U5_20: C25.1, C30.1, U5.20
NET_U6_2: C18.1, R17.1, U6.2
NET_U6_5: C17.1, R16.1, U6.5
NET_U7_5: C19.1, C20.1, R18.1, R19.1, U7.5
NET_U12_1: C34.1, U12.1
NET_U12_6: R21.2, R22.1, U12.6
NET_U12_8: R20.1, U12.8
NET_U13_1: R24.1, R25.1, U13.1
NET_U13_3: R26.2, R27.1, U13.3
NET_U13_4: R23.1, U13.4, U16.2, U17.2
NET_U14_1: R2.1, U14.1, U14.2
PROC_GPIO_TO_U4_SPI_IRQ: R15.1, U1.2, U4.4
PROC_I2S2_CK: U1.6, U5.7
PROC_I2S2_EXT_SD: U1.35, U5.10
PROC_I2S2_SD: U1.36, U5.8
PROC_I2S2_WS: U1.33, U5.9, U5.11
PROC_PC0: U1.8, U18.2
PROC_PC1: U1.9, U18.3
PROC_SPI1_MISO: U1.22, U4.8
PROC_SPI1_MOSI: U1.23, U4.9
PROC_SPI1_NSS: R13.1, U1.20, U4.10
PROC_SPI1_SCK: R14.1, U1.21, U4.7
VCC_S1_15V0: C35.1, C38.1, C39.1, J1.1, R20.2, U12.4
VCC_TIER1_3V3: C1.1, C2.1, C3.1, C4.1, C5.1, C6.1, C7.1, C12.1, C13.1, C14.1, C15.1, C16.1, C21.1, C22.1, C23.1, C24.1, C26.1, C27.1, C28.1, C29.1, C33.1, C36.1, C37.1, C40.1, C41.1, F1.2, R4.2, R5.2, R6.2, R7.2, R8.2, R9.2, R11.2, R12.2, R13.2, R21.1, R23.2, R24.2, R26.1, U1.1, U1.19, U1.32, U1.48, U1.64, U2.5, U2.25, U2.27, U3.14, U4.5, U5.3, U5.5, U5.12, U5.18, U11.4, U12.5, U13.6, U16.5, U17.5
